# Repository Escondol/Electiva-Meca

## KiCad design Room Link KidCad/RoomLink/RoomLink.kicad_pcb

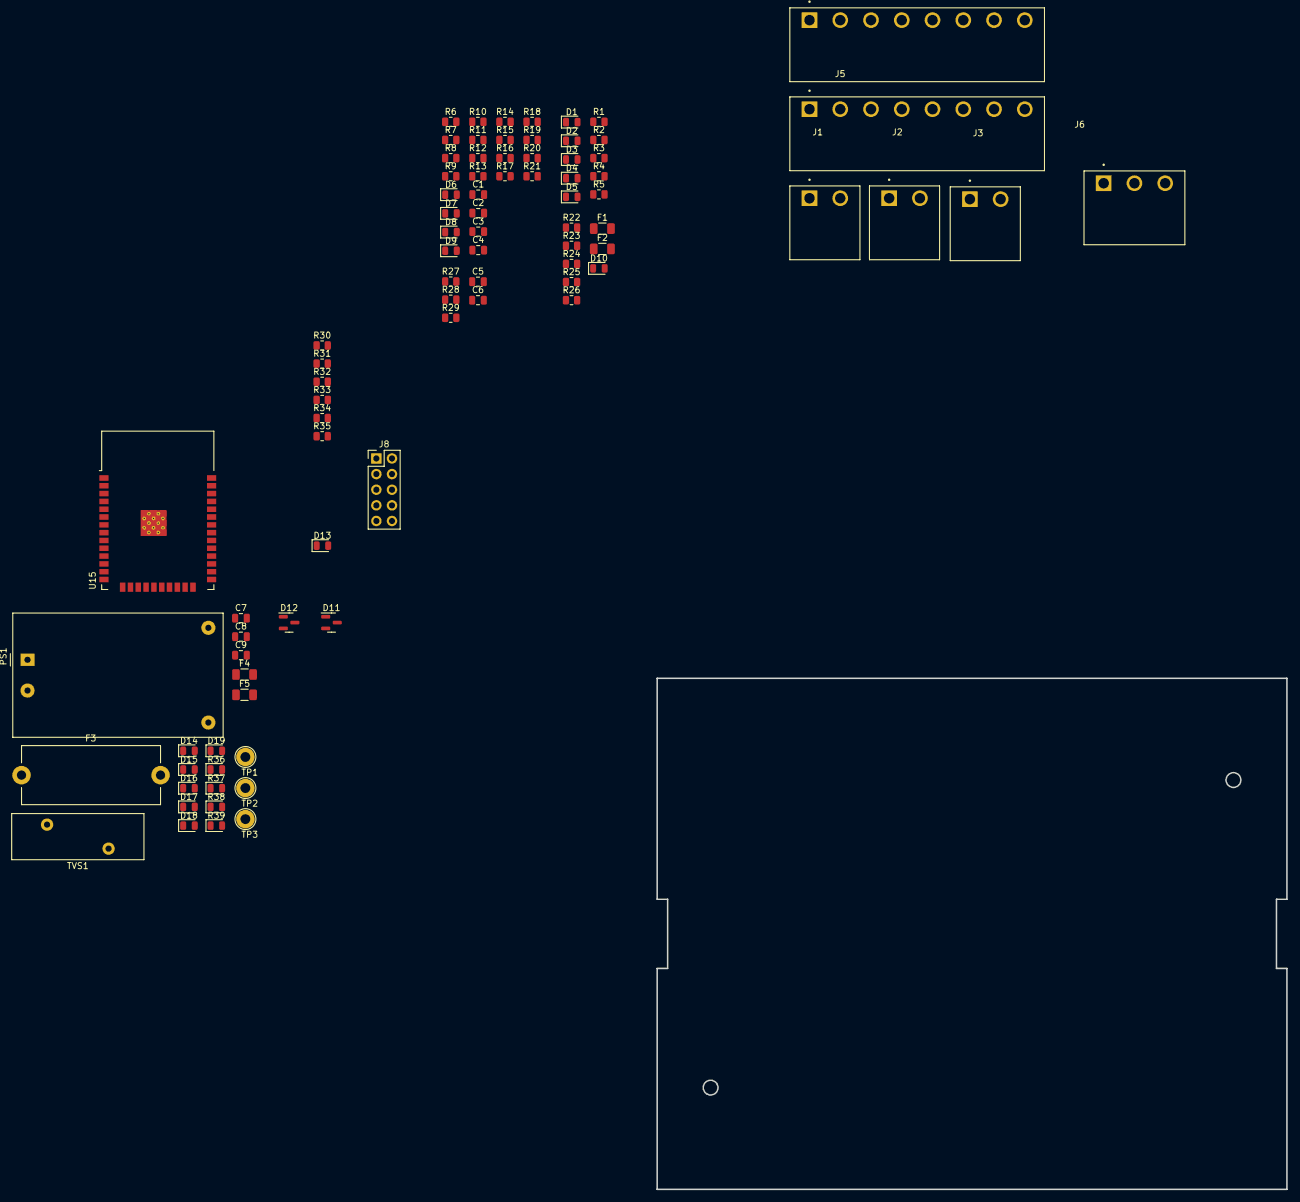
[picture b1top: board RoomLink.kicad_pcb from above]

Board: 2 copper layers, 102.4 x 83.1 mm, 85 parts (0 on the bottom side), 52 nets, no tracks yet.

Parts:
C1, C2, C3, C4: 0.1uF; C_0805_2012Metric
C5: 1uF 25V; C_0805_2012Metric
C6: 0.1uF 50V; C_0805_2012Metric
C7: 0.33uF/25V; C_0805_2012Metric
C8: 2.2uF/25V; C_0805_2012Metric
C9: 47uF/10V; C_0805_2012Metric
D1, D2, D3, D4, D5, D6, D7, D8, D9, D10: LED; LED_0805_2012Metric
D11, D12: SM712_SOT23; SOT-23
D13, D14, D16, D17, D19: LED; D_0805_2012Metric
D15, D18: 1SMA5918BT3G; D_0805_2012Metric
F1, F2, F4, F5: PTS120660V010; Fuse_1206_3216Metric
F3: Fuse; Fuseholder_Cylinder-5x20mm_Stelvio-Kontek_PTF78_Horizontal_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
J1, J2, J3: TBP04R12-500-02BE; CUI_TBP04R12-500-02BE
J4, J5: TBP04R12-500-08BE; CUI_TBP04R12-500-08BE
J6: TBP04R12-500-03BE; CUI_TBP04R12-500-03BE
J8: Conn_ARM_JTAG_SWD_10; PinHeader_2x05_P2.54mm_Vertical
PS1: HLK-PM12; Converter_ACDC_HiLink_HLK-PMxx
R1, R2, R3, R4, R5: 1K; R_0805_2012Metric
R6, R10, R14, R16: 330; R_0805_2012Metric
R7, R11, R15, R17, R25, R26, R28, R29: 10; R_0805_2012Metric
R8, R13, R20, R21, R30: 470; R_0805_2012Metric
R9, R12, R18, R19, R31, R32, R33, R34, R35: 10k; R_0805_2012Metric
R22, R23, R24: 2.2k; R_0805_2012Metric
R27: 10 1%; R_0805_2012Metric
R36, R39: R; D_0805_2012Metric
R37: 2.2K; D_0805_2012Metric
R38: 470; D_0805_2012Metric
TP1, TP2, TP3: TestPoint; TestPoint_Loop_D2.60mm_Drill1.6mm_Beaded
TVS1: RV_Disc_D21.5mm_W7.5mm_P10mm
U15: ESP32-WROOM-32

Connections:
+3.3V: J8.1 (VTref), R31.1, R32.1, R33.1, R34.1, R35.1, U15.2 (VDD)
+5V: C5.1, C6.1, R8.1, R9.1, R12.1, R13.1, R18.1, R19.1, R20.1, R21.1
+12V: C7.1, F4.2, PS1.4 (+Vout), R1.2, R2.2, R3.2, R4.2, R5.2, R37.1, TP2.1
/Room Link/CON-A-: F2.2, J6.2
/Room Link/CON-B+: F1.2, J6.3
/Room Link/CON-DC+: F4.1, J2.1, R36.1
/Room Link/CON-DC-: D14.1 (K), F5.1, J2.2
/Room Link/CON-IN1-: J5.7, R7.1
/Room Link/CON-IN2-: J5.5, R11.1
/Room Link/CON-IN3-: J5.3, R15.1
/Room Link/CON-IN4-: J5.1, R17.1
/Room Link/CON-L1: F3.1, J1.1
/Room Link/CON-LCDA-: J3.1, R29.2
/Room Link/CON-LCDB+: J3.2, R28.2
/Room Link/CON-NEUT: J1.2, PS1.1 (AC/L), TVS1.2
/Room Link/CONTROL/COM_RS485_LCD: R27.1, U15.6 (IO34)
/Room Link/INPUTS/INPUT_1_MCRO: C1.1, D6.1 (K), R9.2
/Room Link/INPUTS/INPUT_2_MCRO: C2.1, D7.1 (K), R12.2
/Room Link/INPUTS/INPUT_3_MCRO: C3.1, D8.1 (K), R18.2
/Room Link/INPUTS/INPUT_4_MCRO: C4.1, D9.1 (K), R19.2
/Room Link/RGND: D10.1 (K), D11.3 (common), J6.1, R24.1
EN: J8.10 (~RESET), R35.2, U15.3 (EN)
GND: C1.2, C2.2, C3.2, C4.2, C5.2, C6.2, C7.2, C8.2, C9.2, D12.3 (common), D15.2 (C), D16.1 (K), D17.1 (K), D18.2 (C), D19.1 (K), F5.2, J8.3 (GND), J8.5 (GND), J8.9 (GNDDetect), PS1.3 (-Vout), TP1.1, U15.1 (GND), U15.15 (GND), U15.38 (GND), U15.39 (GND)
GND1: R7.2, R11.2, R15.2, R17.2
unnamed: D1.2 (A), R5.1
unnamed: D2.2 (A), R4.1
unnamed: D3.2 (A), R3.1
unnamed: D4.2 (A), R2.1
unnamed: D5.2 (A), R1.1
unnamed: D6.2 (A), R8.2
unnamed: D7.2 (A), R13.2
unnamed: D8.2 (A), R20.2
unnamed: D9.2 (A), R21.2
unnamed: D10.2 (A), R23.2
unnamed: D11.1 (A1), R24.2, R25.1
unnamed: D11.2 (A2), R22.2, R26.1
unnamed: D12.1 (A1), R28.1
unnamed: D12.2 (A2), R29.1
unnamed: D13.2 (A), R30.1
unnamed: D14.2 (A), R36.2
unnamed: D16.2 (A), R37.2
unnamed: D17.2 (A), R38.2
unnamed: D19.2 (A), R39.2
unnamed: F1.1, R25.2
unnamed: F2.1, R26.2
unnamed: F3.2, PS1.2 (AC/N), TVS1.1
unnamed: R22.1, R23.1
TCK: J8.4 (SWDCLK/TCK), R31.2, U15.16 (IO13)
TDI: J8.8 (NC/TDI), R34.2, U15.14 (IO12)
TDO: J8.6 (SWO/TDO), R33.2, U15.23 (IO15)
TMS: J8.2 (SWDIO/TMS), R32.2, U15.13 (IO14)
VDD: C8.1, C9.1, D15.1 (A), D18.1 (A), R6.1, R10.1, R14.1, R16.1, R30.2, R38.1, R39.1, TP3.1

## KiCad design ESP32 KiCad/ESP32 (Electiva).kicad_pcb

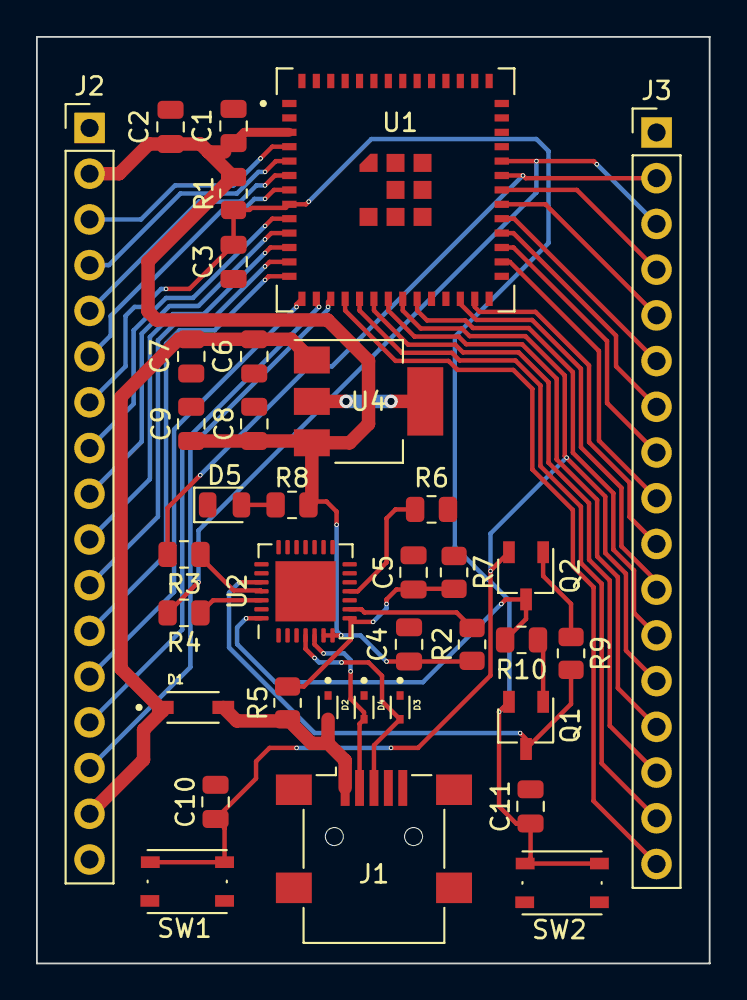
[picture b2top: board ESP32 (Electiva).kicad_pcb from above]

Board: 2 copper layers, 37.4 x 51.5 mm, 36 parts (0 on the bottom side), 45 nets.

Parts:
C1, C6, C9, C10, C11: 0.1uF/50V; C_0805_2012Metric
C2, C4, C7, C8: 10uF/25V; C_0805_2012Metric
C3, C5: 1uF/16V; C_0805_2012Metric
D1: 1N5819HW-7-F; SOD3715X145N
D2, D3, D4: LESD5D5.0CT1G; TVS_LESD5D5.0CT1G
D5: LED; LED_0805_2012Metric
J1: USB_B_Micro; USB_Mini-B_Lumberg_2486_01_Horizontal
J2, J3: Screw_Terminal_01x17; PinHeader_1x17_P2.54mm_Vertical
Q1, Q2: Q_NPN_BCE; TSOT-23
R1, R6, R9, R10: 10K; R_0805_2012Metric
R2: 1K; R_0805_2012Metric
R3, R4: 0; R_0805_2012Metric
R5, R8: 22.1K; R_0805_2012Metric
R7: 47.5K; R_0805_2012Metric
SW1, SW2: SW_Push; SW_Push_1P1T_NO_Vertical_Wuerth_434133025816
U1: ESP32-MINI-1U-N4; MODULE_ESP32-MINI-1U-N4
U2: CP2102N-Axx-xQFN28; QFN-28-1EP_5x5mm_P0.5mm_EP3.35x3.35mm
U4: LT1129-3.3_SOT223; SOT-223-3_TabPin2

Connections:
+3V3: C1.2, C2.2, C4.2, C8.1, C9.1, J2.2, R1.2, R2.1, R8.2, U1.3 (3V3), U2.6 (VDD), U2.7 (VREGIN), U4.3 (VO)
+5V: C6.1, C7.1, D1.C, J2.16, U4.1 (VI)
DN: D4.2, J1.2 (D-), U2.5 (D-)
DTR: Q2.3 (E), R10.2, U2.28 (~DTR)
ESP_RST: C3.2, C11.1, J2.7, Q1.2 (C), R1.1, SW2.2, U1.8 (EN)
GND: C1.1, C2.1, C3.1, C4.1, C5.2, C6.2, C7.2, C8.2, C9.2, C10.2, C11.2, D2.1, D3.1, D4.1, D5.1 (K), J1.5 (GND), J1.6 (Shield), J2.1, J2.17, J3.1, R6.2, R7.1, SW1.1, SW2.1, U1.1 (GND_1), U1.2 (GND_1), U1.27 (GND_1), U1.38 (GND_1), U1.39 (GND_1), U1.40 (GND_1), U1.41 (GND_1), U1.42 (GND_1), U1.43 (GND_1), U1.44 (GND_1), U1.45 (GND_1), U1.46 (GND_1), U1.47 (GND_1), U1.48 (GND_1), U1.49 (GND_1), U1.50 (GND_2), U1.51 (GND_2), U1.52 (GND_2), U1.53 (GND_2), U1.54 (GND_2), U1.55 (GND_2), U1.56 (GND_2), U1.57 (GND_2), U1.58 (GND_2), U1.59 (GND_2), U1.60 (GND_2), U1.61 (GND_2), U1.62 (GND_2), U2.3 (GND), U2.29 (GND), U4.2 (GND)
GPI34: J2.8, U1.9 (I34)
GPI35: J2.9, U1.10 (I35)
GPI36: J2.3, U1.4 (I36)
GPI37: J2.4, U1.5 (I37)
GPI38: J2.5, U1.6 (I38)
GPI39: J2.6, U1.7 (I39)
GPIO00: C10.1, J3.13, Q2.2 (C), SW1.2, U1.21 (IO0)
GPIO02: J3.14, U1.20 (IO2)
GPIO04: J3.12, U1.22 (IO4)
GPIO05: J3.9, U1.29 (IO5)
GPIO09: J3.11, U1.25 (IO9)
GPIO10: J3.10, U1.26 (IO10)
GPIO12: J3.17, U1.17 (IO12)
GPIO13: J3.16, U1.18 (IO13)
GPIO14: J2.15, U1.16 (IO14)
GPIO15: J3.15, U1.19 (IO15)
GPIO18: J3.8, U1.30 (IO18)
GPIO19: J3.6, U1.32 (IO19)
GPIO21: J3.4, U1.34 (IO21)
GPIO22: J3.5, U1.33 (IO22)
GPIO23: J3.7, U1.31 (IO23)
GPIO25: J2.12, U1.13 (IO25)
GPIO26: J2.13, U1.14 (IO26)
GPIO27: J2.14, U1.15 (IO27)
GPIO32: J2.10, U1.11 (IO32)
GPIO33: J2.11, U1.12 (IO33)
unnamed: D5.2 (A), R8.1
unnamed: Q1.1 (B), R10.1
unnamed: Q2.1 (B), R9.1
unnamed: R3.1, U2.25 (RXD)
unnamed: R4.1, U2.26 (TXD)
unnamed: C5.1, R5.2, R7.2, U2.8 (VBUS)
unnamed: R2.2, U2.9 (~RST)
unnamed: R6.1, U2.11 (~SUSPEND)
RTS: Q1.3 (E), R9.2, U2.24 (~RTS)
RX: J3.2, R3.2, U1.35 (RXD0)
TX: J3.3, R4.2, U1.36 (TXD0)
USB_DP: D3.2, J1.3 (D+), U2.4 (D+)
VBUS: D1.A, D2.2, J1.1 (VBUS), R5.1

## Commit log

2023-05-19 Tarea de comandos realizada
2023-05-19 Actualizacion de repositorio
2023-05-19 Repositorio para tareas
2023-05-19 Eliminados comandos
2023-05-19 Carpeta de comandos añadida
2023-05-19 Se añade el capitulo 4
2023-05-19 Se actualiza Capitulo 4
2023-05-19 Actualizacion de las imagenes del capitulo 4
2023-05-26 Se ha añadido los capitulos 5
2023-05-26 Se ha añadido plantilla de requisitos
2023-05-26 Se ha actualizado el word
2023-05-26 Se ha actualizado plantilla de requisitos
2023-05-26 Se ha actualizado el documento
2023-06-03 Se ha añadido el esquematico y layout del ESP32 diseñado por Dojanni Contreras en KiCad
2023-07-17 Se ha avanzado el esquematico
2023-07-29 Se ha realizado el AP
2023-07-29 Se ha editado el readme
